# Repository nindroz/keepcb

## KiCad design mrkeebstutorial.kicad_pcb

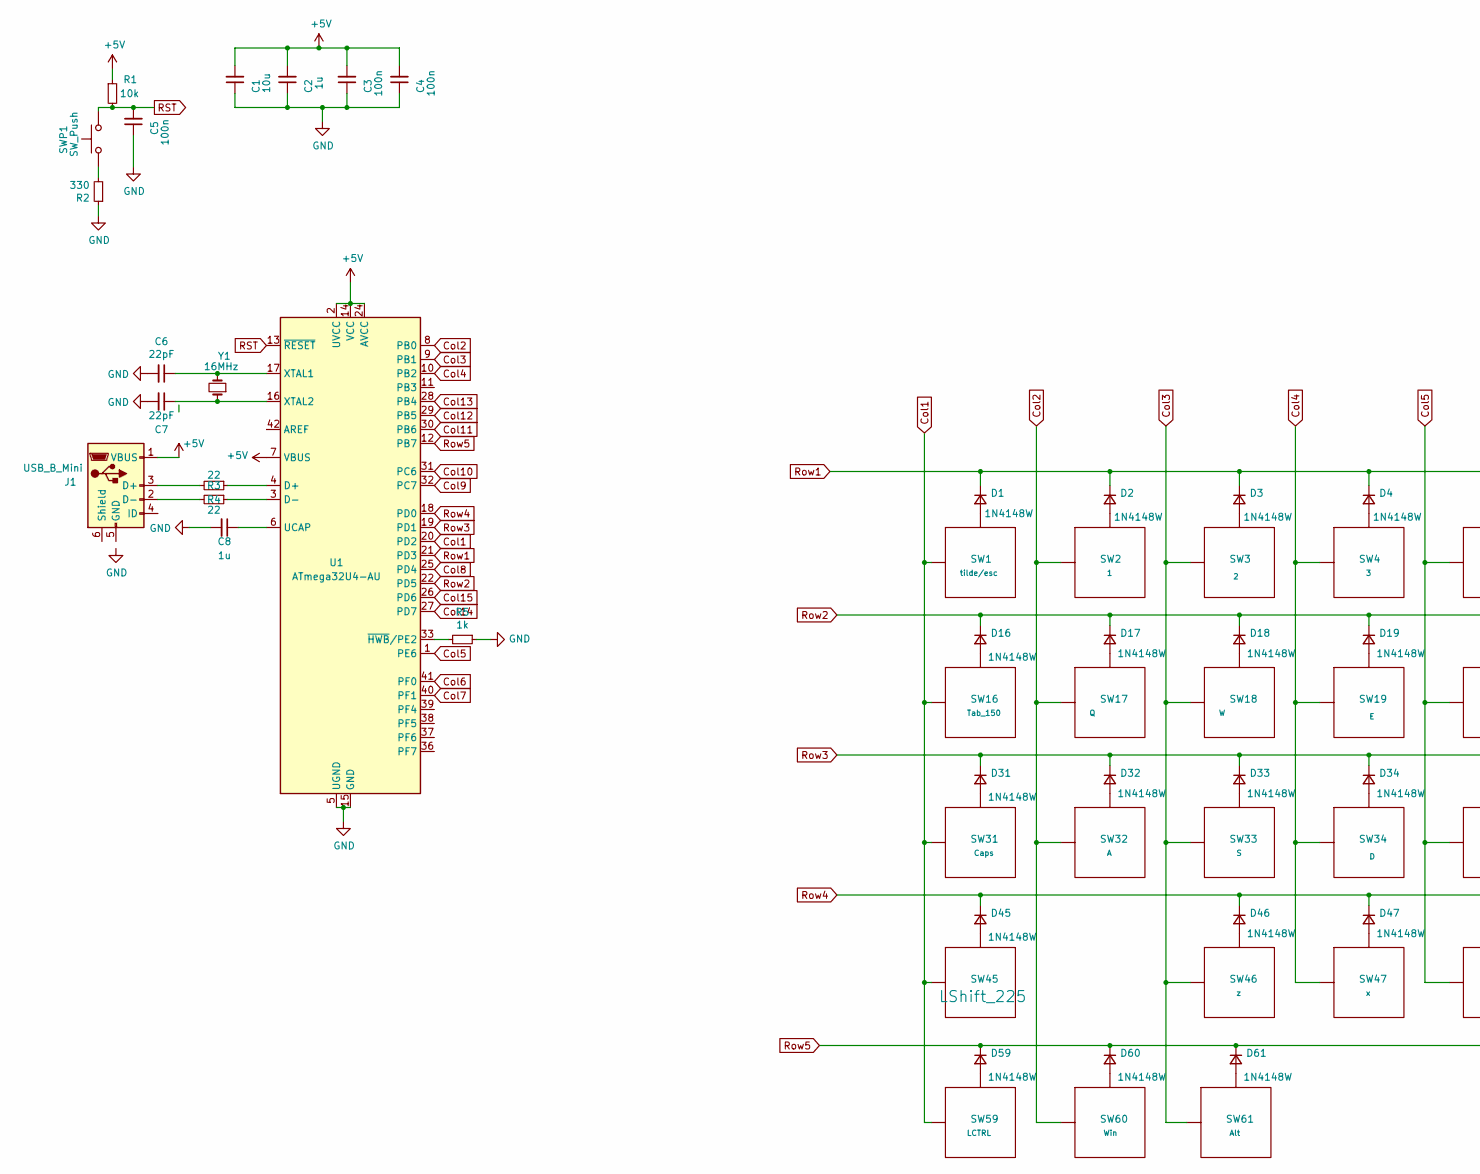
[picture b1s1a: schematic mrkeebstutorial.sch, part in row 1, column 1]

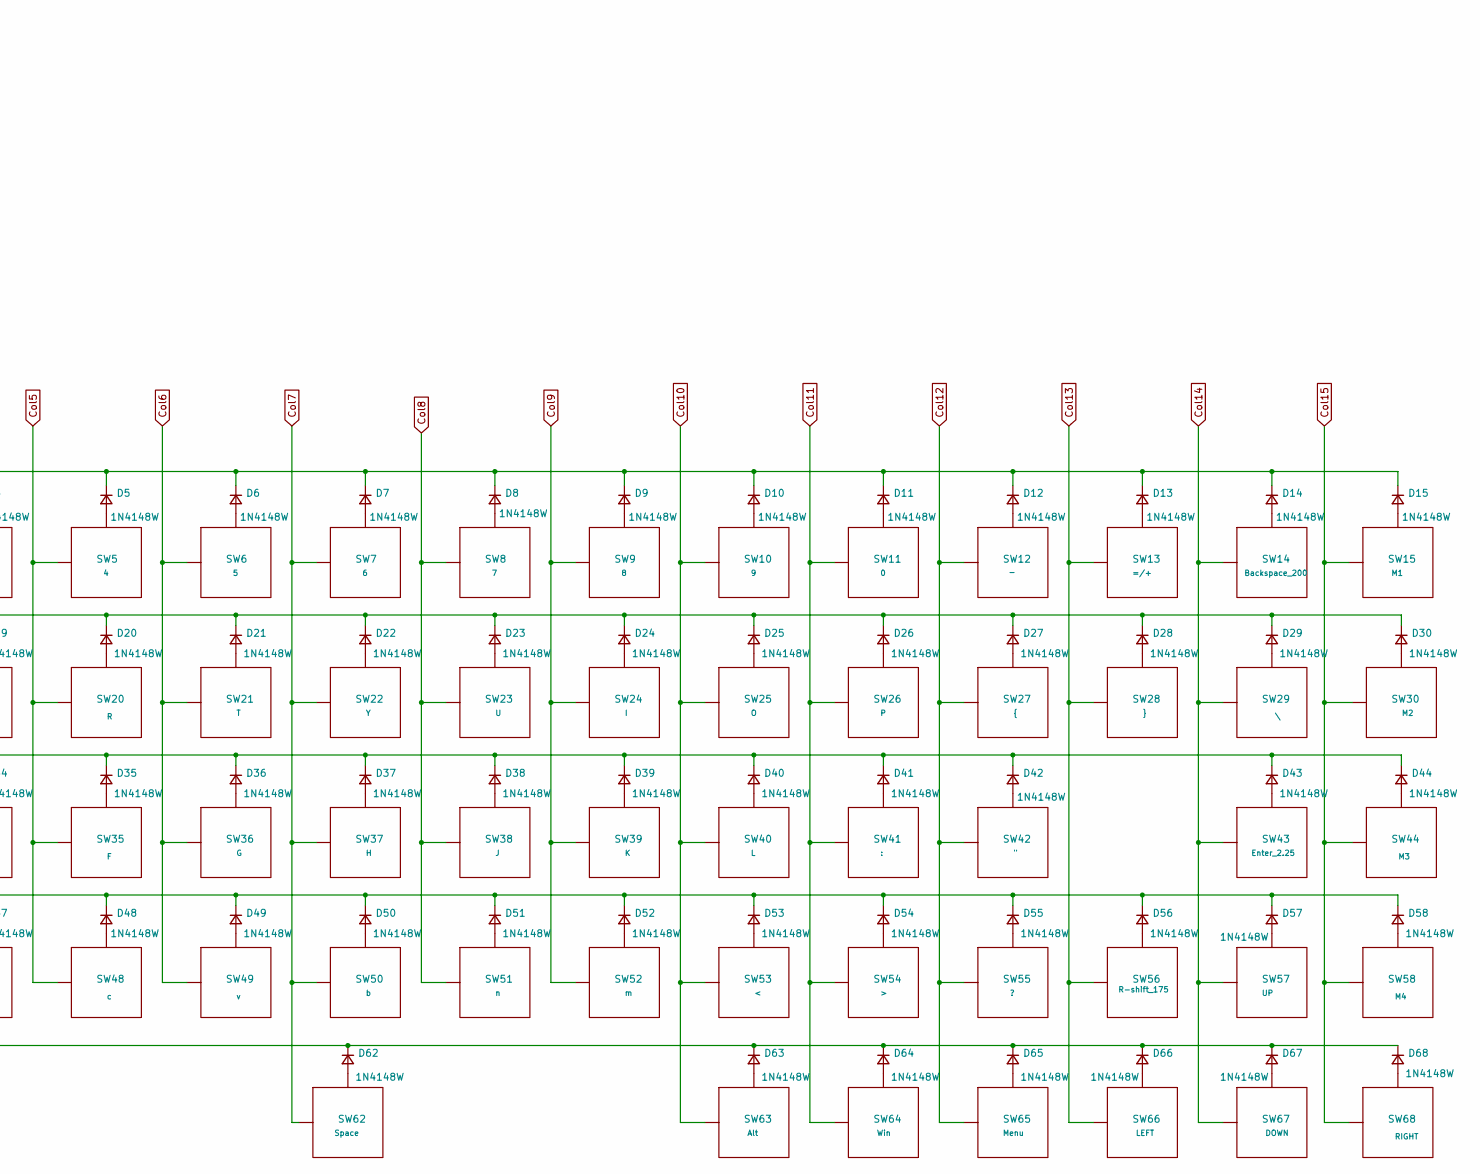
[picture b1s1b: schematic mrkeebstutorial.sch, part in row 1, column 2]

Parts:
C1: 10u; C_0805_2012Metric_Pad1.15x1.40mm_HandSolder; LCSC C1713
C2, C8: 1u; C_0805_2012Metric_Pad1.15x1.40mm_HandSolder; LCSC C28323
C3, C4, C5: 100n; C_0805_2012Metric_Pad1.15x1.40mm_HandSolder; LCSC C129690
C6, C7: 22pF; C_0805_2012Metric_Pad1.15x1.40mm_HandSolder; LCSC C465168
D1, D2, D3, D4, D5, D6, D7, D8, D9, D10, D11, D12, D13, D14, D15, D16, D17, D18, D19, D20, D21, D22, D23, D24, D25, D26, D27, D28, D29, D30, D31, D32, D33, D34, D35, D36, D37, D38, D39, D40, D41, D42, D43, D44, D45, D46, D47, D48, D49, D50, D51, D52, D53, D54, D55, D56, D57, D58, D59, D60, D61, D62, D63, D64, D65, D66, D67, D68: 1N4148W; D_SOD-123; LCSC C402213
J1: USB_B_Mini; USB_MiniB_XM7D-0512
R1: 10k; R_0805_2012Metric_Pad1.15x1.40mm_HandSolder; LCSC C104602
R2: 330; R_0805_2012Metric_Pad1.15x1.40mm_HandSolder; LCSC C104769
R3, R4: 22; R_0805_2012Metric_Pad1.15x1.40mm_HandSolder; LCSC C399501
R5: 1k; R_0805_2012Metric_Pad1.15x1.40mm_HandSolder; LCSC C510146
SW1: tilde/esc; MX100
SW2: 1; MX100
SW3: 2; MX100
SW4: 3; MX100
SW5: 4; MX100
SW6: 5; MX100
SW7: 6; MX100
SW8: 7; MX100
SW9: 8; MX100
SW10: 9; MX100
SW11: 0; MX100
SW12: _; MX100
SW13: =/+; MX100
SW14: Backspace_200; MX200
SW15: M1; MX100
SW16: Tab_150; MX150
SW17: Q; MX100
SW18: W; MX100
SW19: E; MX100
SW20: R; MX100
SW21: T; MX100
SW22: Y; MX100
SW23: U; MX100
SW24: I; MX100
SW25: O; MX100
SW26: P; MX100
SW27: {; MX100
SW28: }; MX100
SW29: \\; MX150
SW30: M2; MX100
SW31: Caps; MX175
SW32: A; MX100
SW33: S; MX100
SW34: D; MX100
SW35: F; MX100
SW36: G; MX100
SW37: H; MX100
SW38: J; MX100
SW39: K; MX100
SW40: L; MX100
SW41: :; MX100
SW42: \"; MX100
SW43: Enter_2.25; MX225
SW44: M3; MX100
SW45: LShift_225; MX225
SW46: z; MX100
SW47: x; MX100
SW48: c; MX100
SW49: v; MX100
SW50: b; MX100
SW51: n; MX100
SW52: m; MX100
SW53: <; MX100
SW54: >; MX100
SW55: ?; MX100
SW56: R-shift_175; MX175
SW57: UP; MX100
SW58: M4; MX100
SW59: LCTRL; MX125
SW60: Win; MX125
SW61: Alt; MX125
SW62: Space; MX625R
SW63: Alt; MX100
SW64: Win; MX100
SW65: Menu; MX100
SW66: LEFT; MX100
SW67: DOWN; MX100
SW68: RIGHT; MX100
SWP1: SW_Push; PushButton_6x6mm_TH
U1: ATmega32U4-AU; TQFP-44_10x10mm_P0.8mm; LCSC C44854
Y1: 16MHz; Crystal_SMD_5032-2Pin_5.0x3.2mm_HandSoldering; LCSC C115962

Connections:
+5V: C1.2, C2.2, C3.2, C4.2, J1.1 (VBUS), R1.1, U1.2 (UVCC), U1.7 (VBUS), U1.14 (VCC), U1.24 (AVCC), U1.34 (VCC), U1.44 (AVCC)
Col1: SW1.1 (Col), SW16.1 (Col), SW31.1 (Col), SW45.1 (Col), SW59.1 (Col), U1.20 (PD2)
Col2: SW2.1 (Col), SW17.1 (Col), SW32.1 (Col), SW60.1 (Col), U1.8 (PB0)
Col3: SW3.1 (Col), SW18.1 (Col), SW33.1 (Col), SW46.1 (Col), SW61.1 (Col), U1.9 (PB1)
Col4: SW4.1 (Col), SW19.1 (Col), SW34.1 (Col), SW47.1 (Col), U1.10 (PB2)
Col5: SW5.1 (Col), SW20.1 (Col), SW35.1 (Col), SW48.1 (Col), U1.1 (PE6)
Col6: SW6.1 (Col), SW21.1 (Col), SW36.1 (Col), SW49.1 (Col), U1.41 (PF0)
Col7: SW7.1 (Col), SW22.1 (Col), SW37.1 (Col), SW50.1 (Col), SW62.1 (Col), U1.40 (PF1)
Col8: SW8.1 (Col), SW23.1 (Col), SW38.1 (Col), SW51.1 (Col), U1.25 (PD4)
Col9: SW9.1 (Col), SW24.1 (Col), SW39.1 (Col), SW52.1 (Col), U1.32 (PC7)
Col10: SW10.1 (Col), SW25.1 (Col), SW40.1 (Col), SW53.1 (Col), SW63.1 (Col), U1.31 (PC6)
Col11: SW11.1 (Col), SW26.1 (Col), SW41.1 (Col), SW54.1 (Col), SW64.1 (Col), U1.30 (PB6)
Col12: SW12.1 (Col), SW27.1 (Col), SW42.1 (Col), SW55.1 (Col), SW65.1 (Col), U1.29 (PB5)
Col13: SW13.1 (Col), SW28.1 (Col), SW56.1 (Col), SW66.1 (Col), U1.28 (PB4)
Col14: SW14.1 (Col), SW29.1 (Col), SW43.1 (Col), SW57.1 (Col), SW67.1 (Col), U1.27 (PD7)
Col15: SW15.1 (Col), SW30.1 (Col), SW44.1 (Col), SW58.1 (Col), SW68.1 (Col), U1.26 (PD6)
GND: C1.1, C2.1, C3.1, C4.1, C5.1, C6.2, C7.2, C8.2, R2.1, R5.1, U1.5 (UGND), U1.15 (GND), U1.23 (GND), U1.35 (GND), U1.43 (GND)
unnamed: C6.1, U1.17 (XTAL1), Y1.2
unnamed: C7.1, U1.16 (XTAL2), Y1.1
unnamed: C8.1, U1.6 (UCAP)
unnamed: D1.2 (A), SW1.2 (Row)
unnamed: D2.2 (A), SW2.2 (Row)
unnamed: D3.2 (A), SW3.2 (Row)
unnamed: D4.2 (A), SW4.2 (Row)
unnamed: D5.2 (A), SW5.2 (Row)
unnamed: D6.2 (A), SW6.2 (Row)
unnamed: D7.2 (A), SW7.2 (Row)
unnamed: D8.2 (A), SW8.2 (Row)
unnamed: D9.2 (A), SW9.2 (Row)
unnamed: D10.2 (A), SW10.2 (Row)
unnamed: D11.2 (A), SW11.2 (Row)
unnamed: D12.2 (A), SW12.2 (Row)
unnamed: D13.2 (A), SW13.2 (Row)
unnamed: D14.2 (A), SW14.2 (Row)
unnamed: D15.2 (A), SW15.2 (Row)
unnamed: D16.2 (A), SW16.2 (Row)
unnamed: D17.2 (A), SW17.2 (Row)
unnamed: D18.2 (A), SW18.2 (Row)
unnamed: D19.2 (A), SW19.2 (Row)
unnamed: D20.2 (A), SW20.2 (Row)
unnamed: D21.2 (A), SW21.2 (Row)
unnamed: D22.2 (A), SW22.2 (Row)
unnamed: D23.2 (A), SW23.2 (Row)
unnamed: D24.2 (A), SW24.2 (Row)
unnamed: D25.2 (A), SW25.2 (Row)
unnamed: D26.2 (A), SW26.2 (Row)
unnamed: D27.2 (A), SW27.2 (Row)
unnamed: D28.2 (A), SW28.2 (Row)
unnamed: D29.2 (A), SW29.2 (Row)
unnamed: D30.2 (A), SW30.2 (Row)
unnamed: D31.2 (A), SW31.2 (Row)
unnamed: D32.2 (A), SW32.2 (Row)
unnamed: D33.2 (A), SW33.2 (Row)
unnamed: D34.2 (A), SW34.2 (Row)
unnamed: D35.2 (A), SW35.2 (Row)
unnamed: D36.2 (A), SW36.2 (Row)
unnamed: D37.2 (A), SW37.2 (Row)
unnamed: D38.2 (A), SW38.2 (Row)
unnamed: D39.2 (A), SW39.2 (Row)
unnamed: D40.2 (A), SW40.2 (Row)
unnamed: D41.2 (A), SW41.2 (Row)
unnamed: D42.2 (A), SW42.2 (Row)
unnamed: D43.2 (A), SW43.2 (Row)
unnamed: D44.2 (A), SW44.2 (Row)
unnamed: D45.2 (A), SW45.2 (Row)
unnamed: D46.2 (A), SW46.2 (Row)
unnamed: D47.2 (A), SW47.2 (Row)
unnamed: D48.2 (A), SW48.2 (Row)
unnamed: D49.2 (A), SW49.2 (Row)
unnamed: D50.2 (A), SW50.2 (Row)
unnamed: D51.2 (A), SW51.2 (Row)
unnamed: D52.2 (A), SW52.2 (Row)
unnamed: D53.2 (A), SW53.2 (Row)
unnamed: D54.2 (A), SW54.2 (Row)
unnamed: D55.2 (A), SW55.2 (Row)
unnamed: D56.2 (A), SW56.2 (Row)
unnamed: D57.2 (A), SW57.2 (Row)
unnamed: D58.2 (A), SW58.2 (Row)
unnamed: D59.2 (A), SW59.2 (Row)
unnamed: D60.2 (A), SW60.2 (Row)
unnamed: D61.2 (A), SW61.2 (Row)
unnamed: D62.2 (A), SW62.2 (Row)
unnamed: D63.2 (A), SW63.2 (Row)
unnamed: D64.2 (A), SW64.2 (Row)
unnamed: D65.2 (A), SW65.2 (Row)
unnamed: D66.2 (A), SW66.2 (Row)
unnamed: D67.2 (A), SW67.2 (Row)
unnamed: D68.2 (A), SW68.2 (Row)
unnamed: J1.2 (D-), R4.2
unnamed: J1.3 (D+), R3.2
unnamed: R2.2, SWP1.1
unnamed: R3.1, U1.4 (D+)
unnamed: R4.1, U1.3 (D-)
unnamed: R5.2, U1.33 (~HWB~/PE2)
RST: C5.2, R1.2, SWP1.2, U1.13 (~RESET)
Row1: D1.1 (K), D2.1 (K), D3.1 (K), D4.1 (K), D5.1 (K), D6.1 (K), D7.1 (K), D8.1 (K), D9.1 (K), D10.1 (K), D11.1 (K), D12.1 (K), D13.1 (K), D14.1 (K), D15.1 (K), U1.21 (PD3)
Row2: D16.1 (K), D17.1 (K), D18.1 (K), D19.1 (K), D20.1 (K), D21.1 (K), D22.1 (K), D23.1 (K), D24.1 (K), D25.1 (K), D26.1 (K), D27.1 (K), D28.1 (K), D29.1 (K), D30.1 (K), U1.22 (PD5)
Row3: D31.1 (K), D32.1 (K), D33.1 (K), D34.1 (K), D35.1 (K), D36.1 (K), D37.1 (K), D38.1 (K), D39.1 (K), D40.1 (K), D41.1 (K), D42.1 (K), D43.1 (K), D44.1 (K), U1.19 (PD1)
Row4: D45.1 (K), D46.1 (K), D47.1 (K), D48.1 (K), D49.1 (K), D50.1 (K), D51.1 (K), D52.1 (K), D53.1 (K), D54.1 (K), D55.1 (K), D56.1 (K), D57.1 (K), D58.1 (K), U1.18 (PD0)
Row5: D59.1 (K), D60.1 (K), D61.1 (K), D62.1 (K), D63.1 (K), D64.1 (K), D65.1 (K), D66.1 (K), D67.1 (K), D68.1 (K), U1.12 (PB7)

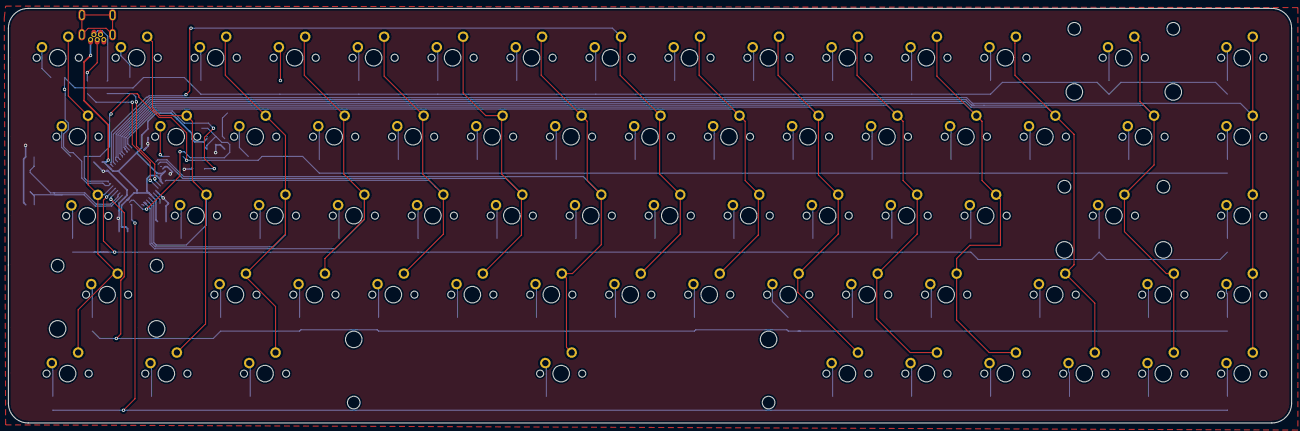
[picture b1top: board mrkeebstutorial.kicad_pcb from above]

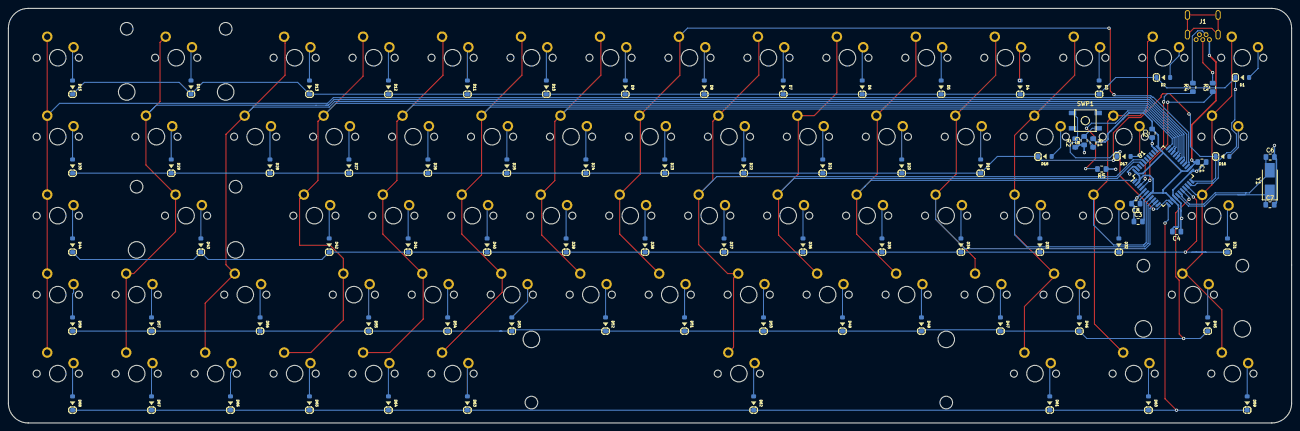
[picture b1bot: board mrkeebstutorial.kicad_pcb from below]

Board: 2 copper layers, 309.6 x 100.0 mm, 153 parts (153 on the bottom side), 100 nets.

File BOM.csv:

Comment,Designator,Footprint,LCSC
"10u","C1","Capacitor_SMD:C_0805_2012Metric_Pad1.15x1.40mm_HandSolder","C15850"
"1u","C2,C8","Capacitor_SMD:C_0805_2012Metric_Pad1.15x1.40mm_HandSolder","C28323"
"100n","C3,C4,C5,C9","Capacitor_SMD:C_0805_2012Metric_Pad1.15x1.40mm_HandSolder","C49678"
"22pF","C6,C7","Capacitor_SMD:C_0805_2012Metric_Pad1.15x1.40mm_HandSolder","C1804"
"1N4148W","D1,D2,D3,D4,D5,D6,D7,D8,D9,D10,D11,D12,D13,D14,D15,D16,D17,D18,D19,D20,D21,D22,D23,D24,D25,D26,D27,D28,D29,D30,D31,D32,D33,D34,D35,D36,D37,D38,D39,D40,D41,D42,D43,D44,D45,D46,D47,D48,D49,D50,D51,D52,D53,D54,D55,D56,D57,D58,D59,D60,D61,D62,D63,D64,D65,D66,D67,D68","acheron_Components:D_SOD-123","C444720"
"USB_B_Mini","J1","acheron_Connectors:USB_MiniB_XM7D-0512",""
"10k","R1","Resistor_SMD:R_0805_2012Metric_Pad1.15x1.40mm_HandSolder","C17414"
"330","R2","Resistor_SMD:R_0805_2012Metric_Pad1.15x1.40mm_HandSolder","C17630"
"22","R3,R4","Resistor_SMD:R_0805_2012Metric_Pad1.15x1.40mm_HandSolder","C17561"
"1k","R5","Resistor_SMD:R_0805_2012Metric_Pad1.15x1.40mm_HandSolder","C17513"
"tilde/esc","SW1","acheron_MX:MX100",""
"9","SW10","acheron_MX:MX100",""
"0","SW11","acheron_MX:MX100",""
"_","SW12","acheron_MX:MX100",""
"=/+","SW13","acheron_MX:MX100",""
"Backspace_200","SW14","acheron_MX:MX200",""
"M1","SW15","acheron_MX:MX100",""
"Tab_150","SW16","acheron_MX:MX150",""
"Q","SW17","acheron_MX:MX100",""
"W","SW18","acheron_MX:MX100",""
"E","SW19","acheron_MX:MX100",""
"1","SW2","acheron_MX:MX100",""
"R","SW20","acheron_MX:MX100",""
"T","SW21","acheron_MX:MX100",""
"Y","SW22","acheron_MX:MX100",""
"U","SW23","acheron_MX:MX100",""
"I","SW24","acheron_MX:MX100",""
"O","SW25","acheron_MX:MX100",""
"P","SW26","acheron_MX:MX100",""
"{","SW27","acheron_MX:MX100",""
"}","SW28","acheron_MX:MX100",""
"\","SW29","acheron_MX:MX150",""
"2","SW3","acheron_MX:MX100",""
"M2","SW30","acheron_MX:MX100",""
"Caps","SW31","acheron_MX:MX175",""
"A","SW32","acheron_MX:MX100",""
"S","SW33","acheron_MX:MX100",""
"D","SW34","acheron_MX:MX100",""
"F","SW35","acheron_MX:MX100",""
"G","SW36","acheron_MX:MX100",""
"H","SW37","acheron_MX:MX100",""
"J","SW38","acheron_MX:MX100",""
"K","SW39","acheron_MX:MX100",""
"3","SW4","acheron_MX:MX100",""
"L","SW40","acheron_MX:MX100",""
":","SW41","acheron_MX:MX100",""
""","SW42","acheron_MX:MX100",""
"Enter_2.25","SW43","acheron_MX:MX225",""
"M3","SW44","acheron_MX:MX100",""
"LShift_225","SW45","acheron_MX:MX225",""
"z","SW46","acheron_MX:MX100",""
"x","SW47","acheron_MX:MX100",""
"c","SW48","acheron_MX:MX100",""
"v","SW49","acheron_MX:MX100",""
"4","SW5","acheron_MX:MX100",""
"b","SW50","acheron_MX:MX100",""
"n","SW51","acheron_MX:MX100",""
"m","SW52","acheron_MX:MX100",""
"<","SW53","acheron_MX:MX100",""
">","SW54","acheron_MX:MX100",""
"?","SW55","acheron_MX:MX100",""
"R-shift_175","SW56","acheron_MX:MX175",""
"UP","SW57","acheron_MX:MX100",""
"M4","SW58","acheron_MX:MX100",""
"LCTRL","SW59","acheron_MX:MX125",""
"5","SW6","acheron_MX:MX100",""
"Win","SW60","acheron_MX:MX125",""
"Alt","SW61","acheron_MX:MX125",""
"Space","SW62","acheron_MX:MX625R",""
"Alt","SW63","acheron_MX:MX100",""
"Win","SW64","acheron_MX:MX100",""
"Menu","SW65","acheron_MX:MX100",""
"LEFT","SW66","acheron_MX:MX100",""
"DOWN","SW67","acheron_MX:MX100",""
"RIGHT","SW68","acheron_MX:MX100",""
"6","SW7","acheron_MX:MX100",""
"7","SW8","acheron_MX:MX100",""
"8","SW9","acheron_MX:MX100",""
"SW_Push","SWP1","random-keyboard-parts:SKQG-1155865","C318884"
"ATmega32U4-AU","U1","Package_QFP:TQFP-44_10x10mm_P0.8mm","C44854"
"16MHz","Y1","Crystal:Crystal_SMD_5032-2Pin_5.0x3.2mm_HandSoldering","C112572"

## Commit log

2020-07-10 first row
2020-07-10 fixed matrix
2020-07-10 fixed matrix juntions
2020-07-10 semi finished scematic
2020-07-10 some shit was doned
2020-07-11 grind done
2020-07-11 ep 3 end
2020-07-11 connecto
2020-07-12 onboard mcu
2020-07-12 final prior to test routing
2020-07-12 diode switch
2020-07-12 finish routing draf
2020-07-12 new route
2020-07-13 routed some lines cleanly
2020-07-13 rearranged
2020-07-13 routed second thing
2020-07-14 caps
2020-07-14 i think done
2020-07-15 resolved vias under pads
2020-07-16 changed ground plane
2020-07-17 migraterd dshit
2020-07-18 changed components for BOM
2020-07-20 final before people check it out
2020-07-20 cleared up old files
2020-07-20 changed stuff
2020-07-22 finare
